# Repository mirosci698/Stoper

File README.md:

Stoper

Projekt semestralny z przedmiotu "Systemy Mikroprocesorowe i Wbudowane". Układ został zbudowany w oparciu o ośmiobitowy
mikrokontroler ATmega8A-PU oraz wyświetlacz znakowy zgodny ze sterownikiem HD44780.  
W projekcie została wykorzystana biblioteka do sterowania wyświetlaczem HD44780 stworzona przez Radosława Kwietnia (http://radzio.dxp.pl/hd44780/).

Nazwy w języku polskim ze względu na wymagania uczelniane projektu.

Stopwatch

Semester project from the "Microprocessor and Embedded Systems". This circuit was based on 8-bit microcontroller ATmega8A-PU and character
display compatible with HD44780 driver.  
In this project I have used HD44780 display library, created by Radosław Kwiecień (http://radzio.dxp.pl/hd44780/).

Names in the Polish language because of the requirements of the university project.  

Video: https://www.youtube.com/watch?v=190qPBOBbLc

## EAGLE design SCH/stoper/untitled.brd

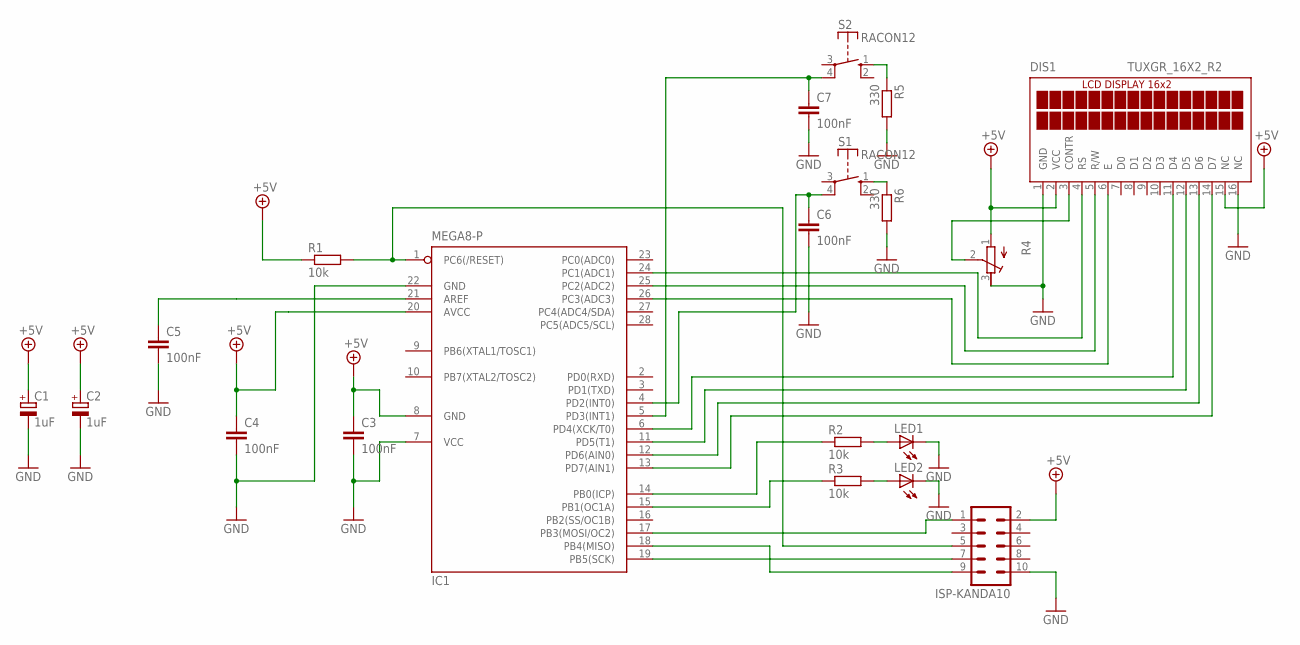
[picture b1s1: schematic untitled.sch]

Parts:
C1: 1uF; E2-5
C2: 1uF; E3,5-8
C3, C4, C5, C6, C7: 100nF; C050-024X044
DIS1: TUXGR_16X2_R2
IC1: MEGA8-P; DIL28-3
ISP-KANDA10: ML10
LED1, LED2: LED3MM
R1, R2, R3: 10k; 0204/7
R4: R-TRIMM3339P; RTRIM3339P
R5, R6: 330; 0204/7
S1, S2: RACON12

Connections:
+5V: C1.+, C2.+, C3.1, C4.1, DIS1.2 (VCC), DIS1.15 (NC), IC1.8 (GND), IC1.20 (AVCC), ISP-KANDA10.2, R1.1, R4.1 (A)
GND: C1.-, C2.-, C3.2, C4.2, C5.2, C6.2, C7.2, DIS1.1 (GND), DIS1.16 (NC), IC1.7 (VCC), IC1.22 (GND), ISP-KANDA10.10, LED1.K (C), LED2.K (C), R4.3 (E), R5.2, R6.2
unnamed: IC1.1 (PC6(/RESET)), ISP-KANDA10.5, R1.2
unnamed: IC1.17 (PB3(MOSI/OC2)), ISP-KANDA10.1
unnamed: IC1.15 (PB1(OC1A)), R3.1
unnamed: IC1.19 (PB5(SCK)), ISP-KANDA10.7
unnamed: IC1.18 (PB4(MISO)), ISP-KANDA10.9
unnamed: C6.1, IC1.4 (PD2(INT0)), S1.4
unnamed: IC1.14 (PB0(ICP)), R2.1
unnamed: LED1.A, R2.2
unnamed: C5.1, IC1.21 (AREF)
unnamed: LED2.A, R3.2
unnamed: DIS1.3 (CONTR), R4.2 (S)
unnamed: DIS1.4 (RS), IC1.24 (PC1(ADC1))
unnamed: DIS1.14 (D7), IC1.13 (PD7(AIN1))
unnamed: DIS1.13 (D6), IC1.12 (PD6(AIN0))
unnamed: DIS1.12 (D5), IC1.11 (PD5(T1))
unnamed: DIS1.11 (D4), IC1.6 (PD4(XCK/T0))
unnamed: DIS1.5 (R/W), IC1.25 (PC2(ADC2))
unnamed: DIS1.6 (E), IC1.26 (PC3(ADC3))
unnamed: C7.1, IC1.5 (PD3(INT1)), S2.4
unnamed: R5.1, S2.1 (S)
unnamed: R6.1, S1.1 (S)

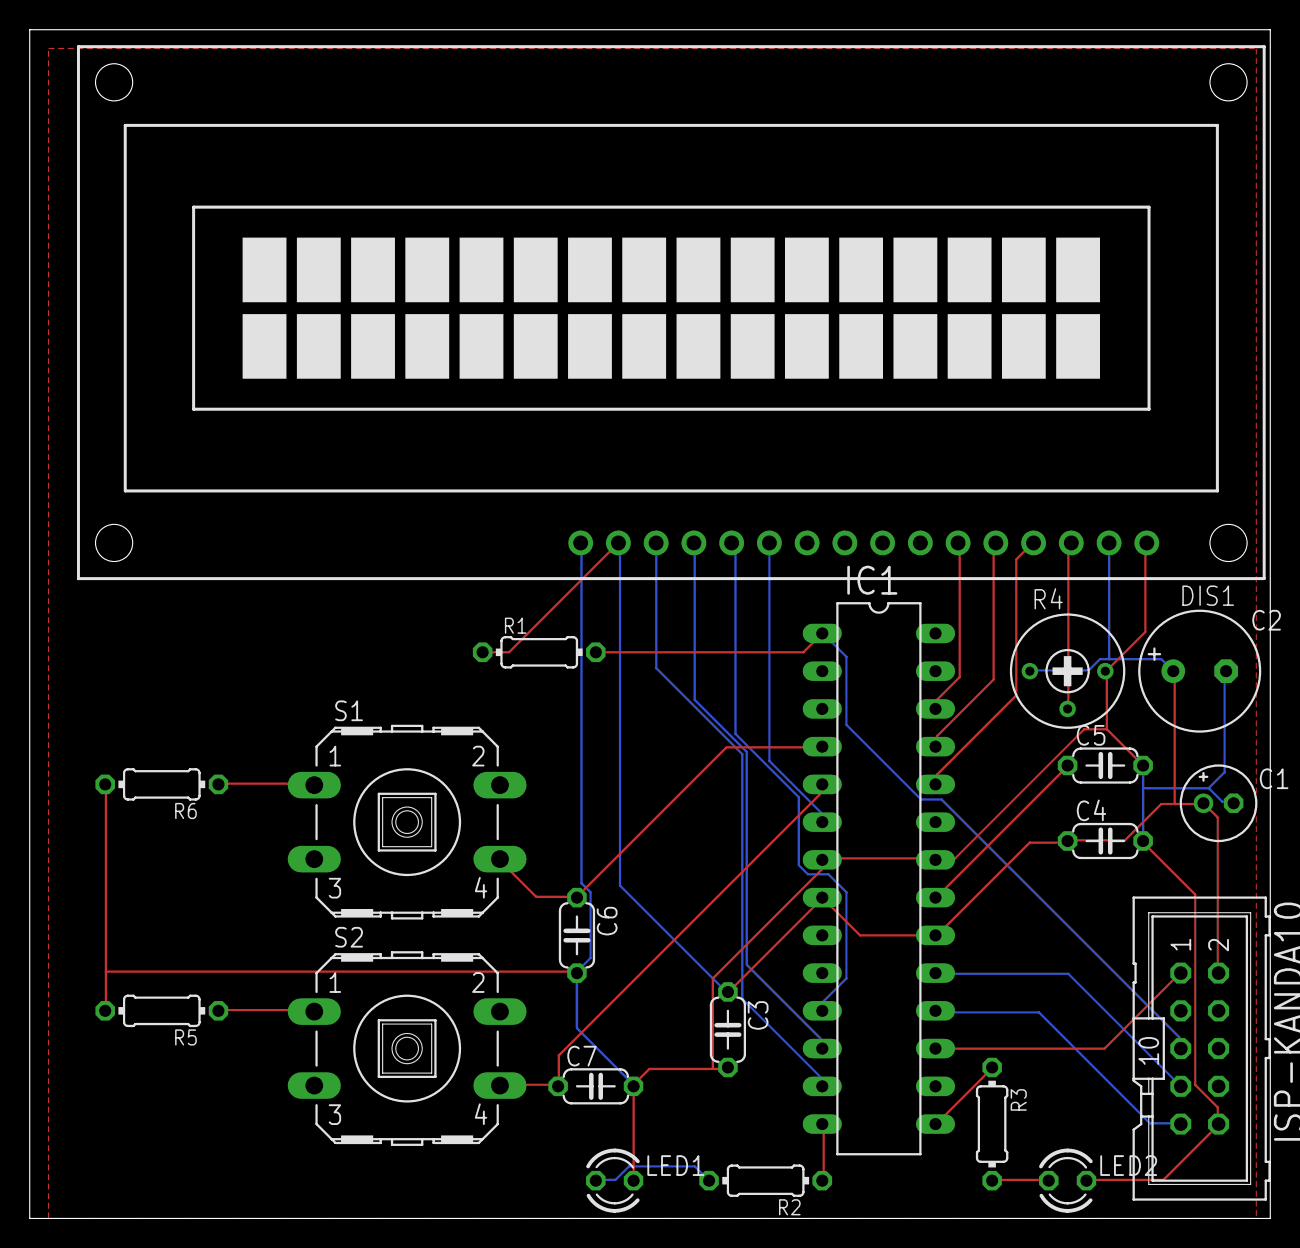
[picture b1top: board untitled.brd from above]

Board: 2 copper layers, 83.5 x 80.0 mm, 20 parts (0 on the bottom side), 23 nets.

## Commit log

2019-08-13 Upload of code
2019-08-13 Added README.md and .gitignore files
2019-08-13 Added video presentation
2019-08-13 Revert "Added video presentation"
    This reverts commit ff7188fd9cf5cef3ecd918ffaebbf83a3b425764.
2019-08-13 Added link to video
